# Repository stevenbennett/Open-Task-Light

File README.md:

# Open Task Light

An open-source desk lamp designed to be extended, repaired, and remade.

> [!WARNING]
> **Before you start:** The Open Task Light is a challenging, hands-on project involving more than 20 printed parts, careful assembly, and thoughtful tuning. Think of your printer less like a magic part replicator and more like a tool to understand and occasionally wrangle. Expect to calibrate, inspect, and sometimes reprint parts to get the right fit and strength. If that kind of problem-solving sounds rewarding, you'll probably enjoy the build. You got this!

## Build an Open Task Light

Choose your build:

- **[Build from a hardware kit](https://opentasklight.com/products/open-task-light-hardware-kit)** — Start with all the hardware you need, print the required parts, and follow the assembly guide.
- **[Source the parts yourself](https://open-task-light.gitbook.io/open-task-light/self-sourcing-guide)** — Use the bills of materials and preparation guides to source, manufacture, and prepare your complete build.

**[Open the complete printing and assembly guide →](https://open-task-light.gitbook.io/open-task-light)**

## Repository contents

This repository contains the 3D models, electronics files, bills of materials, and manufacturing files used to build the Open Task Light.

## Project status

Planned additions include:

- Detailed assembly and preparation instructions for custom cables and processed parts such as the V-slot rails, turntable bearing, and QT Py.
- Drawings and schematics for professionally manufactured components, including sheet-metal parts and PCBs.

## Important design constraint

> **The horizontal arm is intentionally non-reversible.** This is a deliberate constraint related to the patent landscape surrounding this type of mechanism. Proposals to make the arm reversible will not be accepted into this project.

## More on the project

- [Sliding Into Perfection: The Open Task Light — Hackaday](https://hackaday.com/2026/09/01/sliding-into-perfection-the-open-task-light)
- [Building the Open Task Light — James Vaughan](https://jamesbvaughan.com/open-task-light)

## Community

- [Watch the project on YouTube](https://www.youtube.com/channel/UCvnxvXWYcOlmhRFvZ_ISP8g)
- [Join the Discord](https://discord.gg/B43ZVcBme4)
- [Support the project on Patreon](https://www.patreon.com/StevenBennett)

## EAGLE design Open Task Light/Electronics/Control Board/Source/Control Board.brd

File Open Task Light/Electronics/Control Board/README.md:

# Control Board PCB

The Control Board is the primary electronics PCB for the Open Task Light.

For fabrication details, required parts, and assembly instructions, see the [Control Board section of the Open Task Light assembly guide](https://open-task-light.gitbook.io/open-task-light/self-sourcing-guide/custom-manufactured-parts/control-board).

## Files

- `control-board-gerbers.zip` contains the Gerber, solder-mask, solder-paste, silkscreen, board-profile, and drill files required to order the bare PCB.
- `Source/Control Board.brd` and `Source/Control Board.sch` are the editable Autodesk Fusion Electronics source files.
- `Assembly/control-board-bom.csv` is the Fusion Electronics BOM for the components installed on the PCB.
- `Assembly/PnP_Control Board_front.csv` and `Assembly/PnP_Control Board_back.csv` are the front- and back-side pick-and-place exports from Fusion Electronics.

## Manufacturing notes

Upload the Gerber ZIP when ordering the bare PCB. If using an assembly service, you may need to reformat the BOM and placement files to meet the manufacturer's requirements.

The Adafruit QT Py ESP32-S2 is sourced separately and plugs into the headers after the Control Board is assembled. Confirm the board outline, holes, component positions, board sides, rotations, and component polarity in the manufacturer's preview before ordering.

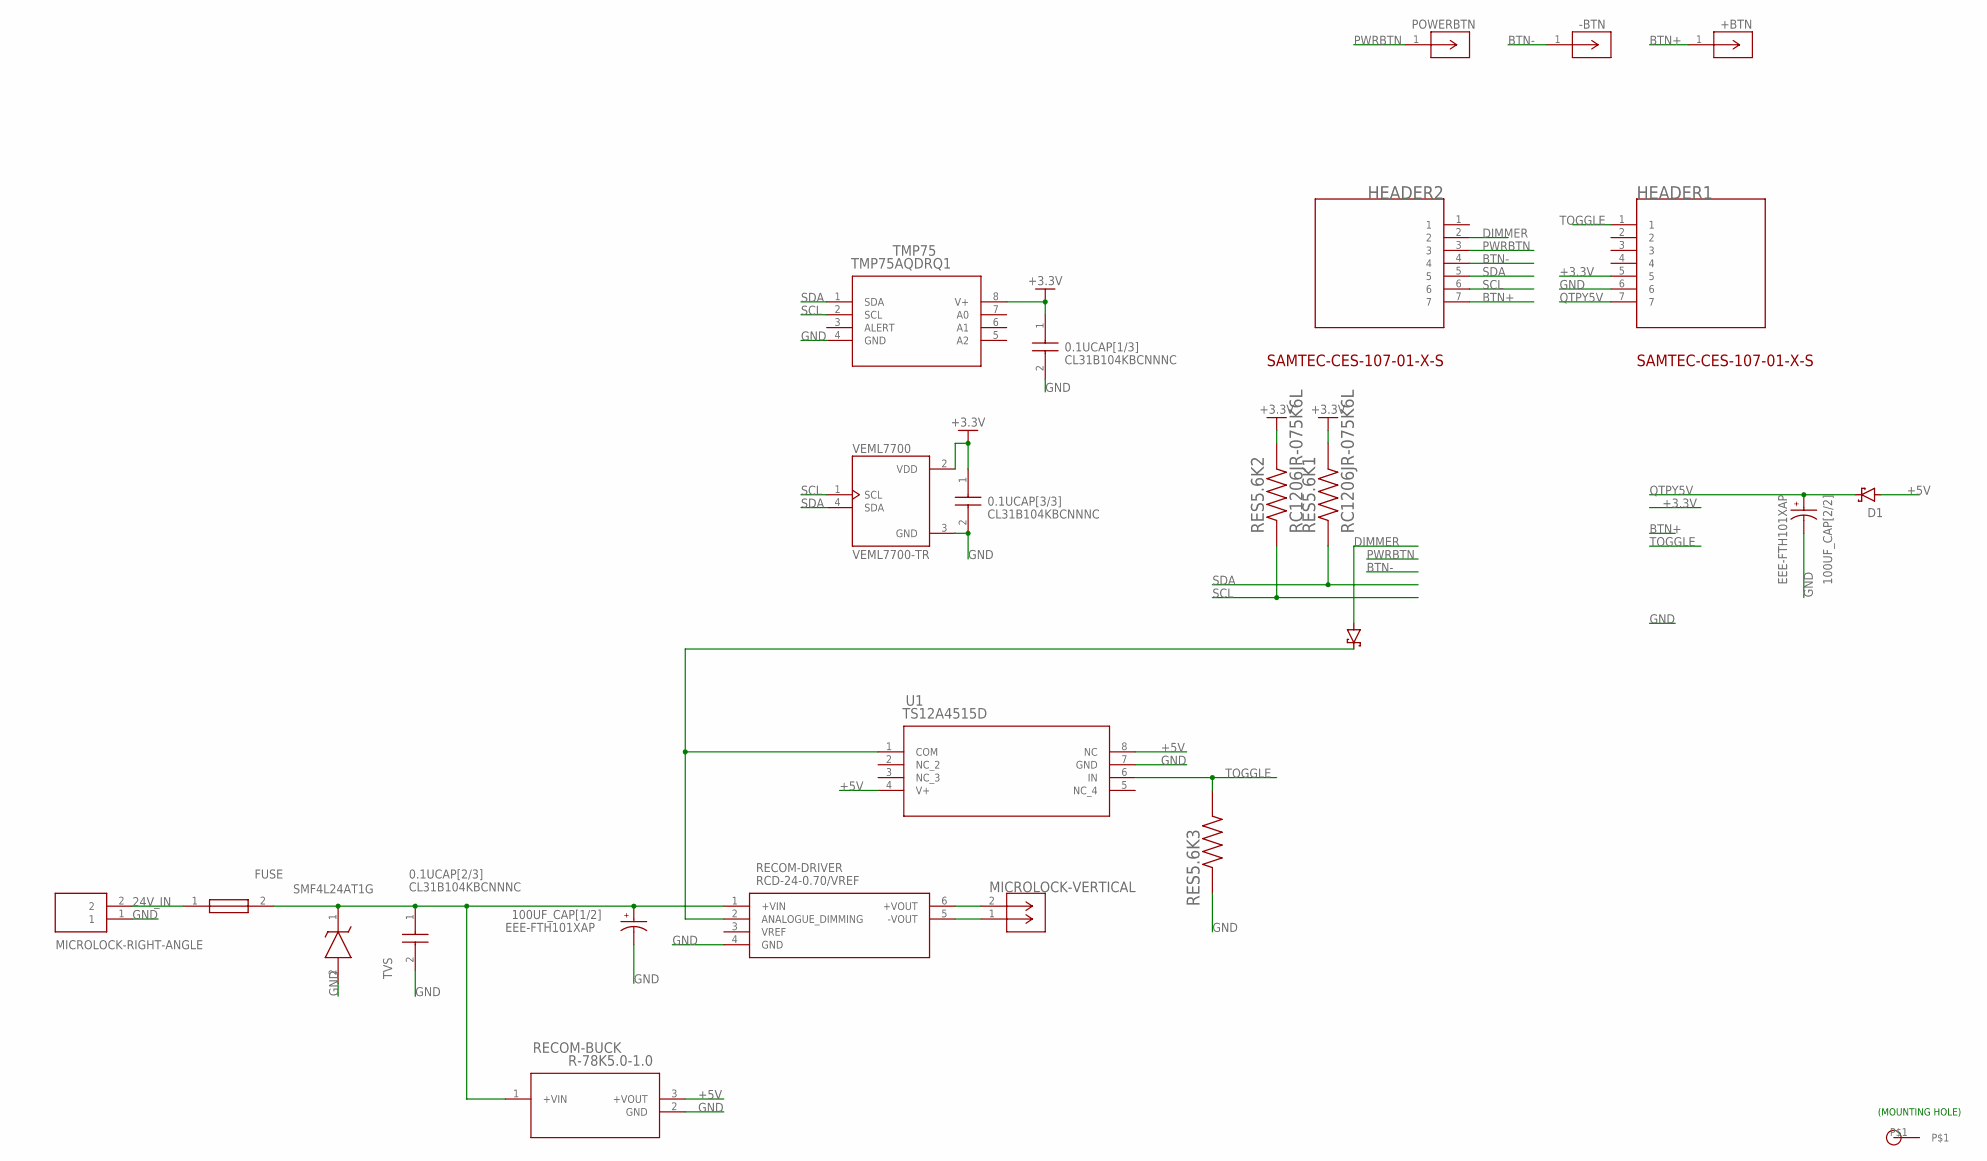
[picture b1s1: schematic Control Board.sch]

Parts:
0.1UCAP[1/3], 0.1UCAP[2/3], 0.1UCAP[3/3]: CL31B104KBCNNNC; CAPC3216X100N; MPN CL31B104KBCNNNC
100UF_CAP[1/2], 100UF_CAP[2/2]: EEE-FTH101XAP; CAP_EEEFTH101XAP; MPN EEE-FTH101XAP
+BTN: 807-22-001-10-001101; CONN_807-22-001-10-001101_MIM; MPN 807-22-001-10-001101
-BTN: 807-22-001-10-001101; CONN_807-22-001-10-001101_MIM; MPN 807-22-001-10-001101
D1, D3: PMEG4010EGWX; SOD-123; MPN PMEG4010EGWX
FUSE: SMD2016B100TF/33; MPN SMD2016B100TF/33
HEADER1, HEADER2: CES-107-01-G-S; SAMTEC-CES-107-01-X-S
MICROLOCK-RIGHT-ANGLE: 2200980271; MPN 2200980271
MICROLOCK-VERTICAL: 2200970271; CONN_2200970000-SD_02_MOL; MPN 2200970271
POWERBTN: 807-22-001-10-001101; CONN_807-22-001-10-001101_MIM; MPN 807-22-001-10-001101
RECOM-BUCK: R-78K5.0-1.0; R-78K5.0-1.0_RCP; MPN R-78K5.0-1.0
RECOM-DRIVER: RCD-24-0.70/VREF; RCD24030; MPN RCD-24-0.70/VREF
RES5.6K1, RES5.6K2, RES5.6K3: RC1206JR-075K6L; RESC3116X65N; MPN RC1206JR-075K6L
TMP75: TMP75AQDRQ1; D8_TEX; MPN TMP75AQDRQ1
TVS: SMF4L24AT1G; SODFL3619X98N
U1: TS12A4515D; D8-L; MPN TS12A4515D
U$2: 2.5MMPLATEDTHROUGHHOLE; 2.5MMPLATEDHOLE
VEML7700: VEML7700-TR; XDCR_VEML7700-TR; MPN VEML7700-TR

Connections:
24V_IN: FUSE.1, MICROLOCK-RIGHT-ANGLE.2
+3.3V: 0.1UCAP[1/3].1, 0.1UCAP[3/3].1, HEADER1.5, RES5.6K1.2, RES5.6K2.2, TMP75.8 (V+), VEML7700.2 (VDD)
+5V: D1.A, RECOM-BUCK.3 (+VOUT), U1.4 (V+), U1.8 (NC)
+24V: 0.1UCAP[2/3].1, 100UF_CAP[1/2].1, FUSE.2, RECOM-BUCK.1 (+VIN), RECOM-DRIVER.1 (+VIN), TVS.1 (K)
A0: D3.C, RECOM-DRIVER.2 (ANALOGUE_DIMMING), U1.1 (COM)
BTN+: +BTN.1, HEADER2.7
BTN-: -BTN.1, HEADER2.4
DIMMER: D3.A, HEADER2.2
GND: 0.1UCAP[1/3].2, 0.1UCAP[2/3].2, 0.1UCAP[3/3].2, 100UF_CAP[1/2].2, 100UF_CAP[2/2].2, HEADER1.6, MICROLOCK-RIGHT-ANGLE.1, RECOM-BUCK.2 (GND), RECOM-DRIVER.4 (GND), RES5.6K3.1, TMP75.4 (GND), TVS.2 (A), U1.7 (GND), VEML7700.3 (GND)
LED+: MICROLOCK-VERTICAL.2 (1), RECOM-DRIVER.6 (+VOUT)
LED-: MICROLOCK-VERTICAL.1 (2), RECOM-DRIVER.5 (-VOUT)
PWRBTN: HEADER2.3, POWERBTN.1
QTPY5V: 100UF_CAP[2/2].1, D1.C, HEADER1.7
SCL: HEADER2.6, RES5.6K2.1, TMP75.2 (SCL), VEML7700.1 (SCL)
SDA: HEADER2.5, RES5.6K1.1, TMP75.1 (SDA), VEML7700.4 (SDA)
TOGGLE: HEADER1.1, RES5.6K3.2, U1.6 (IN)

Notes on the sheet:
(MOUNTING HOLE)

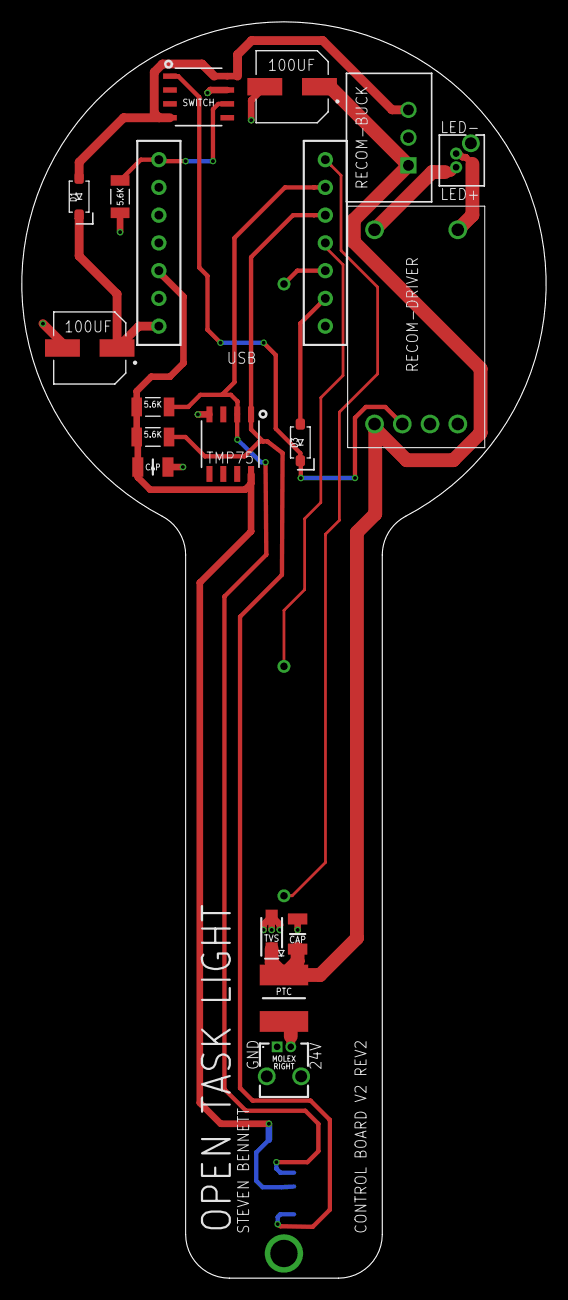
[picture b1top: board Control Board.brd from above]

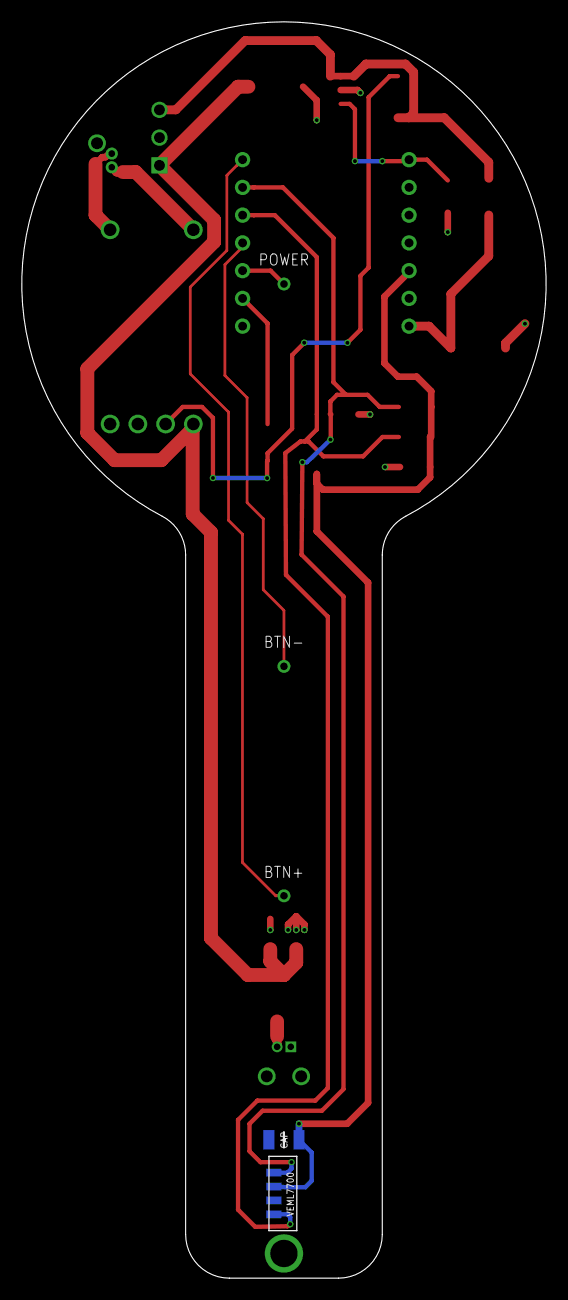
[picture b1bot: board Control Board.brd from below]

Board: 2 copper layers, 48.0 x 115.0 mm, 25 parts (5 on the bottom side), 16 nets.

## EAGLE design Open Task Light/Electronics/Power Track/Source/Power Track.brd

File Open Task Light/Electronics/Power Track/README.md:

# Power Track PCB

The Power Track is the long, two-conductor PCB that carries 24 V along the Open Task Light rails.

For fabrication details, required parts, and assembly instructions, see the [Power Track section of the Open Task Light assembly guide](https://open-task-light.gitbook.io/open-task-light/self-sourcing-guide/custom-manufactured-parts/power-track).

## Files

- `power-track-gerbers.zip` contains the fabrication and drill files required to order the bare PCB.
- `Source/Power Track.brd` and `Source/Power Track.sch` are the editable Autodesk Fusion Electronics source files.
- `Assembly/power-track-bom.csv` is the Fusion Electronics BOM for the two parts installed on the PCB.
- Pick-and-place files are not included because the Power Track is intended to be assembled by hand.

## Manufacturing notes

Upload the Gerber ZIP when ordering the bare PCB. Assemble the surface-mount standoff and right-angle Micro-Lock connector by hand as described in the assembly guide.

Confirm the board outline, plated and non-plated holes, and exposed contact areas in the manufacturer's preview before ordering.

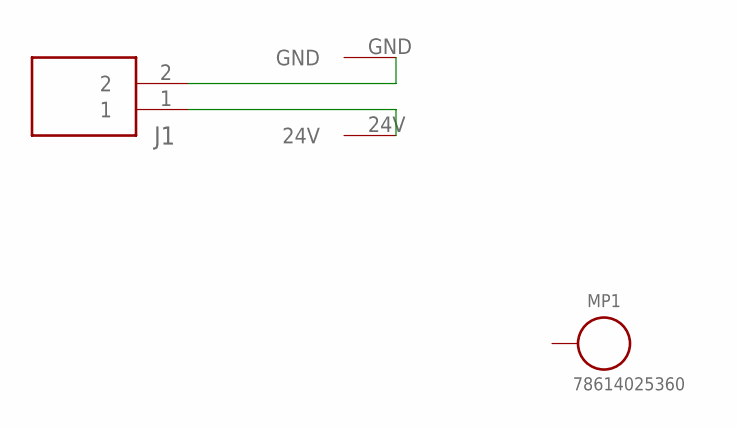
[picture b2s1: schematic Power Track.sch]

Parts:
CONTACT_PADS: POWERTRACKPAD; POWER-TRACK-PADS
J1: 2200980271
MP1: 78614025360; WE-SMSA_78614020360

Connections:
24V: CONTACT_PADS.24V, J1.1
GND: CONTACT_PADS.GND, J1.2

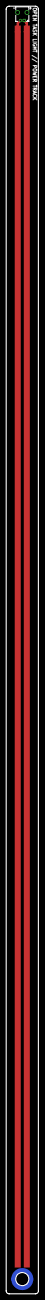
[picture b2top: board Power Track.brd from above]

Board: 2 copper layers, 10.8 x 432.0 mm, 3 parts (1 on the bottom side), 2 nets.

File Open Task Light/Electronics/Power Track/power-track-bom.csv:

Reference,Part,Quantity,Manufacturer,Manufacturer Part Number,Supplier,Supplier Part Number,Source URL,Notes
J1,"Micro-Lock Plus right-angle PCB header - 2 position",1,Molex,2200980271,DigiKey,900-2200980271-ND,https://www.digikey.com/en/products/detail/molex/2200980271/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,"Ideally, epoxy the connector to the PCB before soldering."
MP1,"M3 solderable SMD standoff - 2.5 mm",1,Würth Elektronik,78614025360,DigiKey,732-78614025360CT-ND,https://www.digikey.com/en/products/detail/w%C3%BCrth-elektr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,

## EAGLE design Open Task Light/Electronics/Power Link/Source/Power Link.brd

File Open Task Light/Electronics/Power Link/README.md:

# Power Link PCB

The Power Link is the two-conductor PCB that transfers power between the vertical and horizontal Power Tracks through the carriage.

For fabrication details, required parts, and assembly instructions, see the [Power Link section of the Open Task Light assembly guide](https://open-task-light.gitbook.io/open-task-light/self-sourcing-guide/custom-manufactured-parts/power-link).

## Files

- `power-link-gerbers.zip` contains the Gerber, solder-mask, solder-paste, board-profile, and drill files required to order the bare PCB.
- `Source/Power Link.brd` and `Source/Power Link.sch` are the editable Autodesk Fusion Electronics source files.
- `Assembly/power-link-bom.csv` is the Fusion Electronics BOM for the eight Mill-Max OmniBall spring-loaded contacts.
- `Assembly/PnP_Power Link_front.csv` and `Assembly/PnP_Power Link_back.csv` are the front- and back-side pick-and-place exports from Fusion Electronics.

## Manufacturing notes

Upload the Gerber ZIP when ordering the bare PCB. If using an assembly service, you may need to reformat the BOM and placement files to meet the manufacturer's requirements.

The OmniBall contacts are individual surface-mount parts and are best installed using a reflow process or professional assembly service. Confirm the board outline, holes, component positions, board sides, and rotations in the manufacturer's preview before ordering.

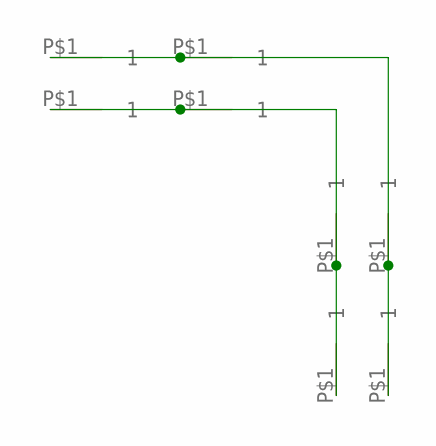
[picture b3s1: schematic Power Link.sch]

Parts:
PIN1, PIN2, PIN3, PIN4, PIN5, PIN6, PIN7, PIN8: 0945-0-15-20-09-14-11-0; MILL_MAX_0945_SMD

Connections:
unnamed: PIN1.P$1, PIN3.P$1, PIN5.P$1, PIN7.P$1
unnamed: PIN2.P$1, PIN4.P$1, PIN6.P$1, PIN8.P$1

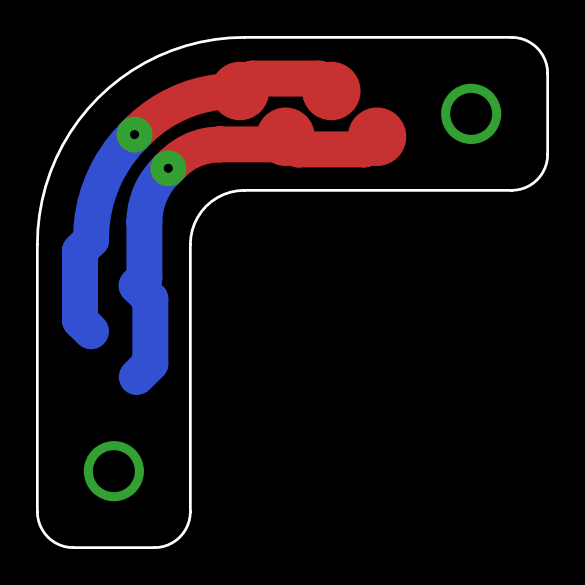
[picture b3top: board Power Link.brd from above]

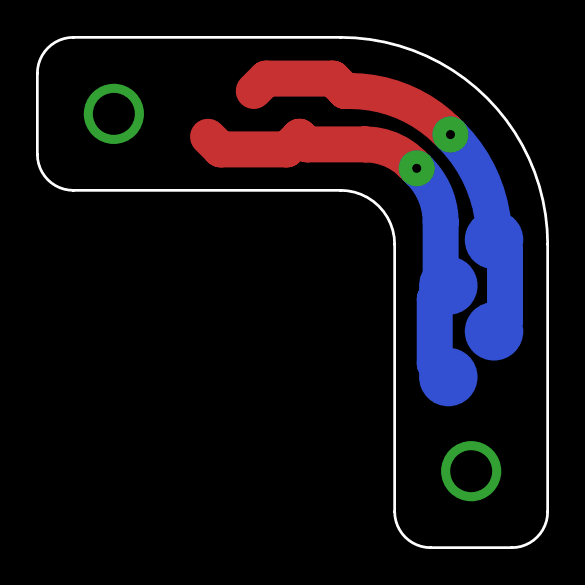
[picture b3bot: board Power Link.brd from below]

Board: 2 copper layers, 28.4 x 28.4 mm, 8 parts (4 on the bottom side), 2 nets.

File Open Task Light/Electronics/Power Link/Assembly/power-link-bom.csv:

Qty,Value,Device,Package,Parts,Description,DATASHEET,MANUFACTURER,MPN
8,0945-0-15-20-09-14-11-0,0945-0-15-20-09-14-11-0,MILL_MAX_0945_SMD,"PIN1, PIN2, PIN3, PIN4, PIN5, PIN6, PIN7, PIN8",Surface Mount Spring-Loaded Pin,https://www.mill-max.com/assets/pdfs/0945.pdf,Mill-Max,0945-0-15-20-09-14-11-0

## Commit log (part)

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2025-07-02 Carriage refinement
    Removed unnecessary chamfer on m5 screw holes (should help keep screws straighter)
2025-07-02 Removing some DIYson references in subdirectories
    DIYson -> Open Task Light
    DIYson Express -> Open Task Light Express
2025-07-02 Carriage countersink depth fix
    Fixed M5 screw countersink depth to work with both 25mm and 27mm M5 screws. Will likely switch to 27mm only in the future.
2025-07-02 Fixed file export
2025-07-04 Clean-up
    Removed some cosmetic fillets added for blender
2025-07-22 Better brightness steps definition and scaling
    Updated when/how brightness steps are calculated.
    - BRIGHTNESS_LEVELS still defines the total number of brightness steps and can be any number but is 4 by default (unchanged from last update)
    - Added GAMMA variable which is used to shift the weight of the brightness scaling. 1 makes an unscaled array [25, 50, 75, 100]. 2 shifts the curve lower. .5 shifts the curve higher. 1.5 works really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
    - BRIGHTNESS_STEPS pre-calculates the weighted steps based on BRIGHTNESS_LEVELS and GAMMA. Probably not necessary but I guess it's nice to just calculate this once rather than every time the brightne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

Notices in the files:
parts and their libraries:
ROUND SPACER M3 STEEL 2.50MM: Copyright: Würth Elektronik
